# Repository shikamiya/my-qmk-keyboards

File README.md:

# my-qmk-keyboards
My keyboards using qmk-firmware and ProMicro

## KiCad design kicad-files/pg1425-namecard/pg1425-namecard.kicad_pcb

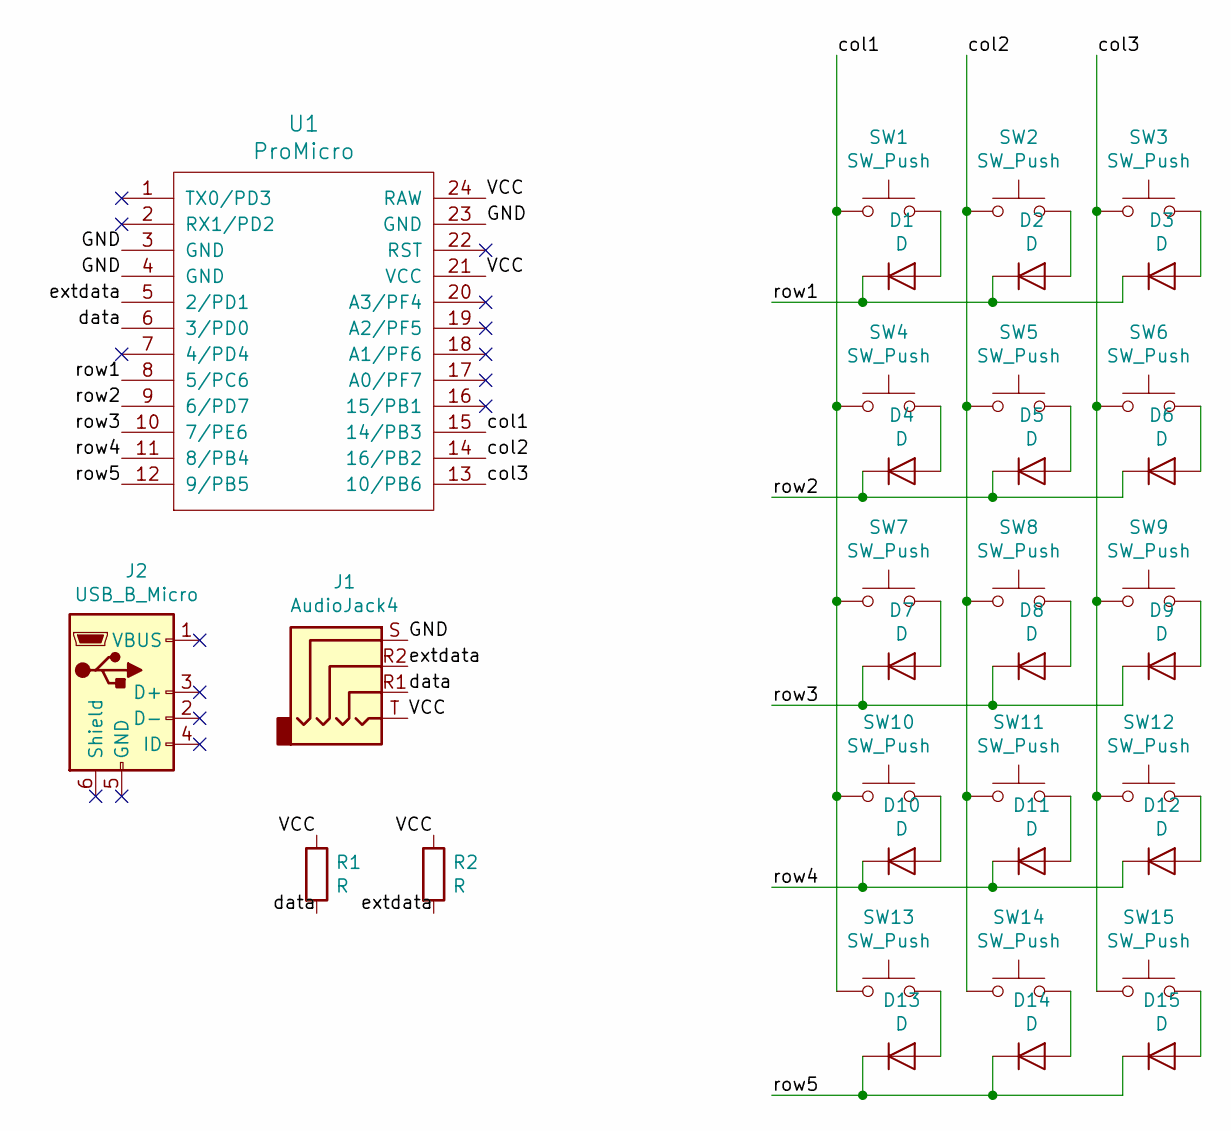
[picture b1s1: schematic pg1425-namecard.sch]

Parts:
D1, D2, D3, D4, D5, D6, D7, D8, D9, D10, D11, D12, D13, D14, D15: D; D_dual-SOD-123-and-DO-35-SOD27-P7.62-Horizontal-with-masked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
J1: AudioJack4; MJ-4PP-9
J2: USB_B_Micro; USB-MicroB-Reversible
R1, R2: R; R_Axial_DIN0207_L6.3mm_D2.5mm_P7.62mm_Horizontal
SW1, SW2, SW3, SW4, SW5, SW6, SW7, SW8, SW9, SW10, SW11, SW12, SW13, SW14, SW15: SW_Push; Kailh-PG1425-X-Switch-reversible-NPTH-margin-0.2-pad2-1.3-d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
U1: ProMicro; ArduinoProMicro

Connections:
/GND: J1.S, U1.3 (GND), U1.4 (GND), U1.23 (GND)
/VCC: J1.T, R1.1, R2.1, U1.21 (VCC), U1.24 (RAW)
/col1: SW1.1, SW4.1, SW7.1, SW10.1, SW13.1, U1.15 (14/PB3)
/col2: SW2.1, SW5.1, SW8.1, SW11.1, SW14.1, U1.14 (16/PB2)
/col3: SW3.1, SW6.1, SW9.1, SW12.1, SW15.1, U1.13 (10/PB6)
/data: J1.R1, R1.2, U1.6 (3/PD0)
/extdata: J1.R2, R2.2, U1.5 (2/PD1)
/row1: D1.1 (K), D2.1 (K), D3.1 (K), U1.8 (5/PC6)
/row2: D4.1 (K), D5.1 (K), D6.1 (K), U1.9 (6/PD7)
/row3: D7.1 (K), D8.1 (K), D9.1 (K), U1.10 (7/PE6)
/row4: D10.1 (K), D11.1 (K), D12.1 (K), U1.11 (8/PB4)
/row5: D13.1 (K), D14.1 (K), D15.1 (K), U1.12 (9/PB5)
unnamed: D1.2 (A), SW1.2
unnamed: D2.2 (A), SW2.2
unnamed: D3.2 (A), SW3.2
unnamed: D4.2 (A), SW4.2
unnamed: D5.2 (A), SW5.2
unnamed: D6.2 (A), SW6.2
unnamed: D7.2 (A), SW7.2
unnamed: D8.2 (A), SW8.2
unnamed: D9.2 (A), SW9.2
unnamed: D10.2 (A), SW10.2
unnamed: D11.2 (A), SW11.2
unnamed: D12.2 (A), SW12.2
unnamed: D13.2 (A), SW13.2
unnamed: D14.2 (A), SW14.2
unnamed: D15.2 (A), SW15.2

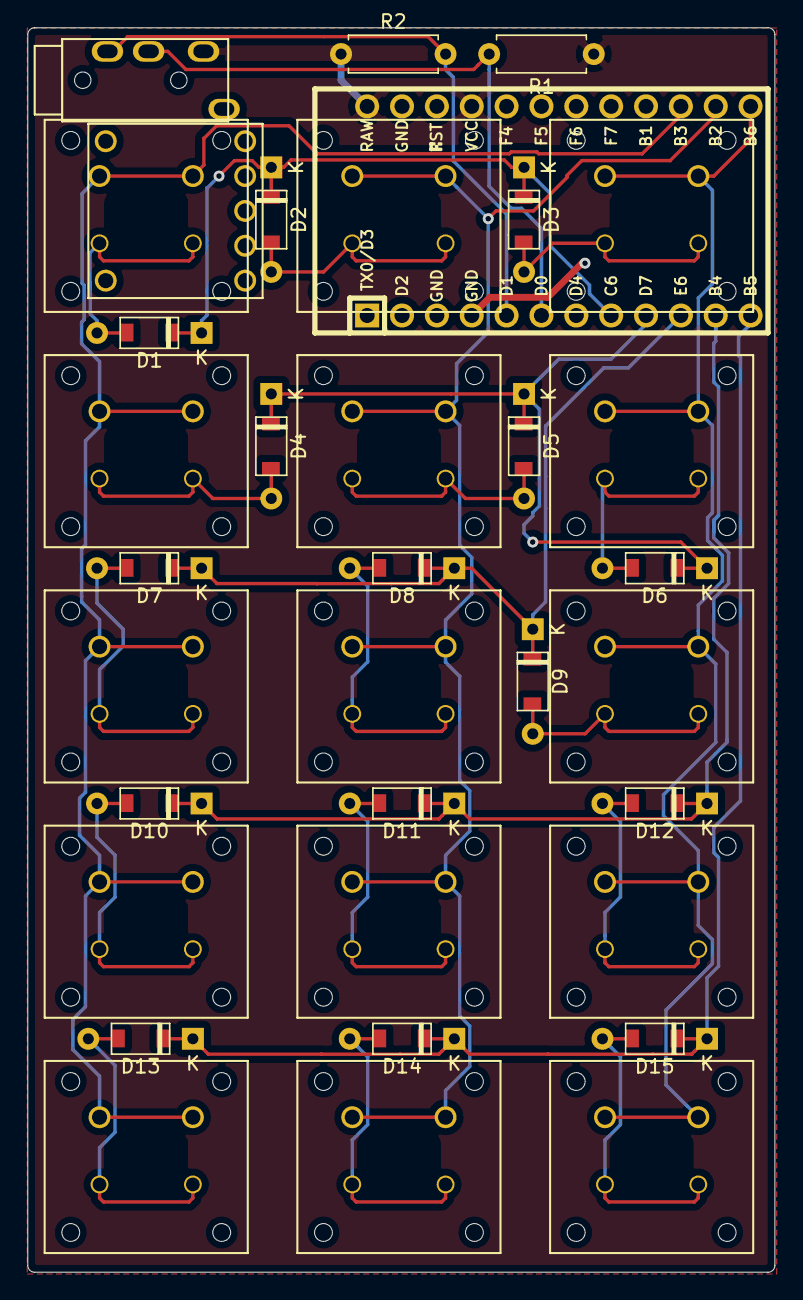
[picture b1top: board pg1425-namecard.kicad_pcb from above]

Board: 2 copper layers, 54.4 x 90.7 mm, 35 parts (0 on the bottom side), 27 nets.

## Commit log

2019-04-19 Add pg1425-namecard pcb files
2019-04-19 Add pg1425_pocket_60 firmware
2019-04-19 Add qmk firmware for pg1425_namecard
2019-04-19 Add pg1425_pocket_30 firmware
2019-05-03 Add new_keyboard for twin_b
2019-07-15 Add double_bridge firmware
2019-07-18 Add split_sample
    - executed `util/new_keyboard.sh`
2019-07-18 Remove some comments
2019-07-18 Update readme of split_sample
2019-07-18 Divide readme by language
2019-07-18 Add new_keyboard script usage
2019-07-19 Change bootloader setting
2019-07-19 Fix title of bootloader setting
2019-07-19 Enable split feature
2019-07-19 Modify split configulation
2019-07-19 Enable LED feature
2019-07-19 Add some text in readme
2019-07-19 Fix typo
2019-07-19 Enable OLED feature
2019-07-19 Reduce firmware size
2019-07-19 Fix spacing of rules.mk
2019-07-19 Fix markdown heading
2019-07-19 Fix readme
2019-07-19 Modify readme
2019-07-19 Disable some more features
2019-07-19 Add default keymap
2019-07-20 Change include of keymap
2019-07-20 Change OLED font
